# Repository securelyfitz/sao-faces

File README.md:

# sao-faces
'Faces' to be used along with ['arms'](https://github.com/securelyfitz/sao-arms) for a build-your-own badge. See the [microbadge](https://github.com/securelyfitz/microbadge) readme for more details about using them.

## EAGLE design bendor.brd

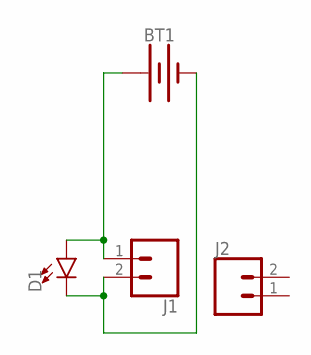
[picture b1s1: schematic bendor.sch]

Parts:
BT1: BATTERY-20MM_SMD_4LEGS; BATTCON_20MM_4LEGS
D1: LED3MM; LED_3MM
J1, J2: CONN_02LOCK; 1X02_LOCK
U$1: OREGON

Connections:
GND: BT1.NEGATIVE (-), D1.K (C), J1.2
VCC: BT1.POSITIVE@1 (+), BT1.POSITIVE@2 (+), BT1.POSITIVE@3 (+), BT1.POSITIVE@4 (+), D1.A, J1.1

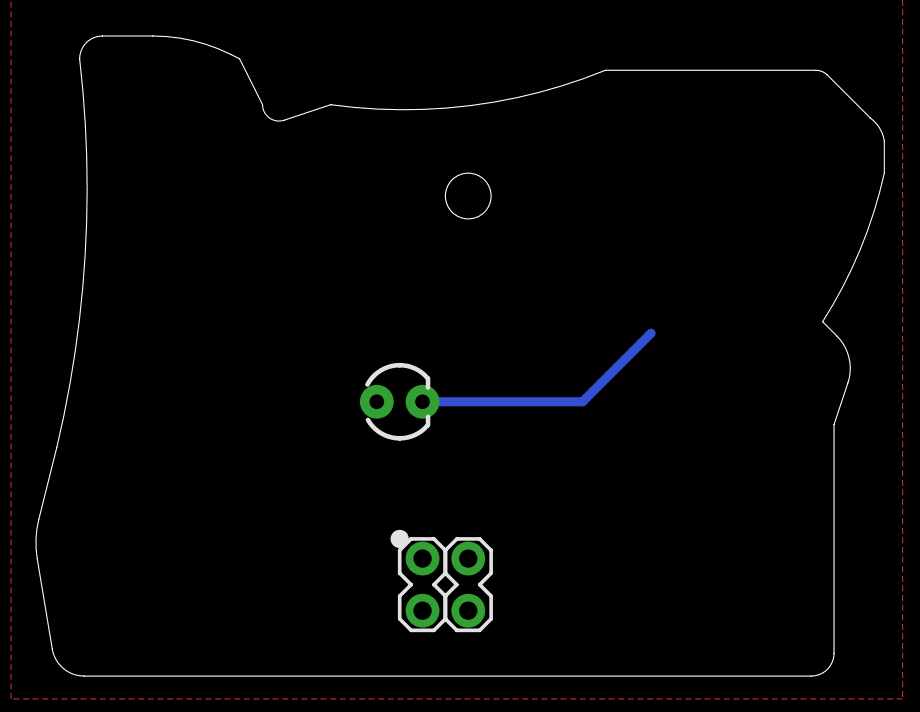
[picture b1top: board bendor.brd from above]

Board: 2 copper layers, 47.1 x 35.6 mm, 5 parts (1 on the bottom side), 2 nets.

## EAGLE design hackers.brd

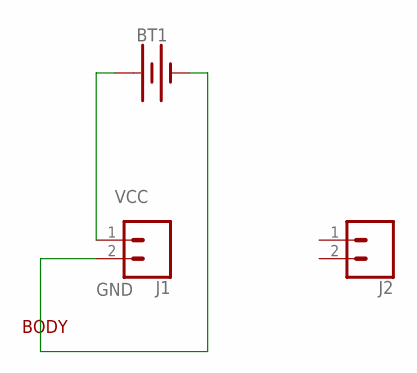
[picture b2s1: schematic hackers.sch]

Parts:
BT1: BATTERY-20MM_SMD; BATTCON_20MM
J1, J2: CONN_02LOCK; 1X02_LOCK
U$1: BODY; HACKERS

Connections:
GND: BT1.2 (-), J1.2
VCC: BT1.1 (+), J1.1

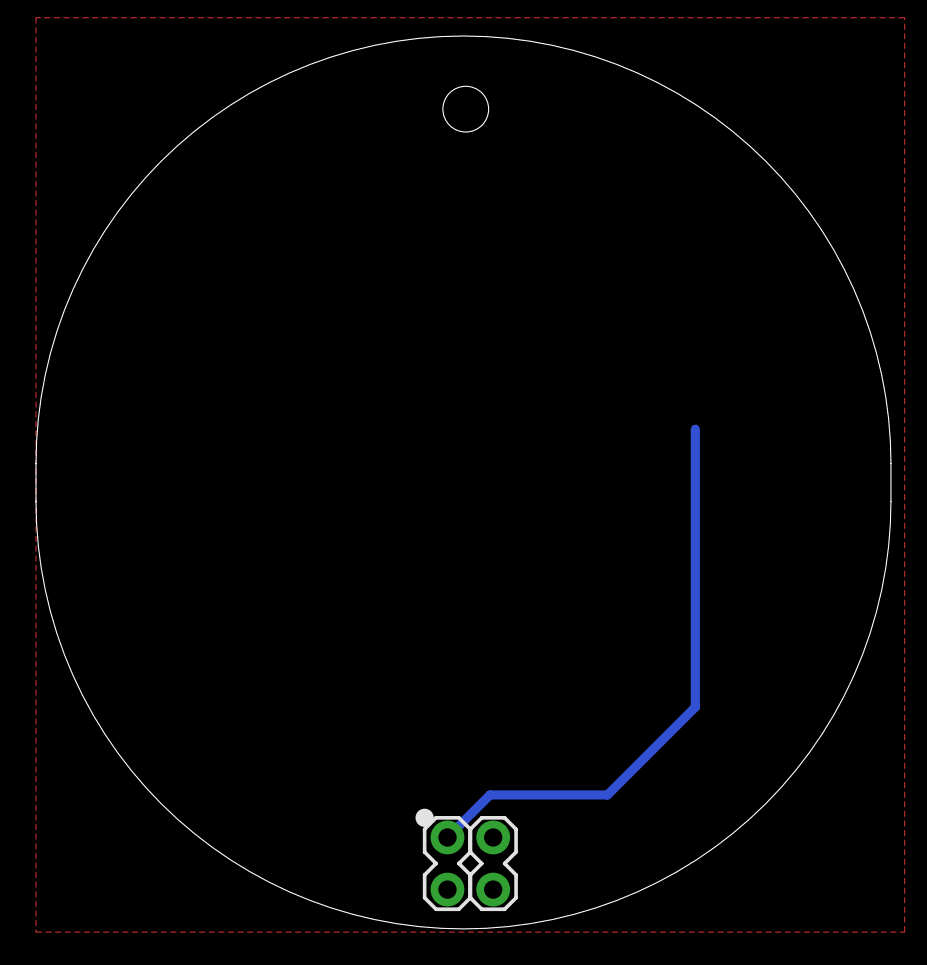
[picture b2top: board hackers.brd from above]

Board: 2 copper layers, 47.5 x 49.6 mm, 4 parts (1 on the bottom side), 2 nets.

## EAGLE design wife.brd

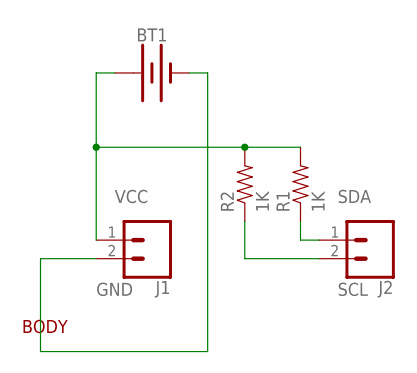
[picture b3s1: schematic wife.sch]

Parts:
BT1: BATTERY-20MM_SMD; BATTCON_20MM
J1, J2: CONN_02LOCK; 1X02_LOCK
R1, R2: 1K; AXIAL-0.3EZ
U$1: BODYWIFE; WIFE

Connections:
GND: BT1.2 (-), J1.2
SCL: J2.2, R2.P$1 (1)
SDA: J2.1, R1.P$1 (1)
VCC: BT1.1 (+), J1.1, R1.P$2 (2), R2.P$2 (2)

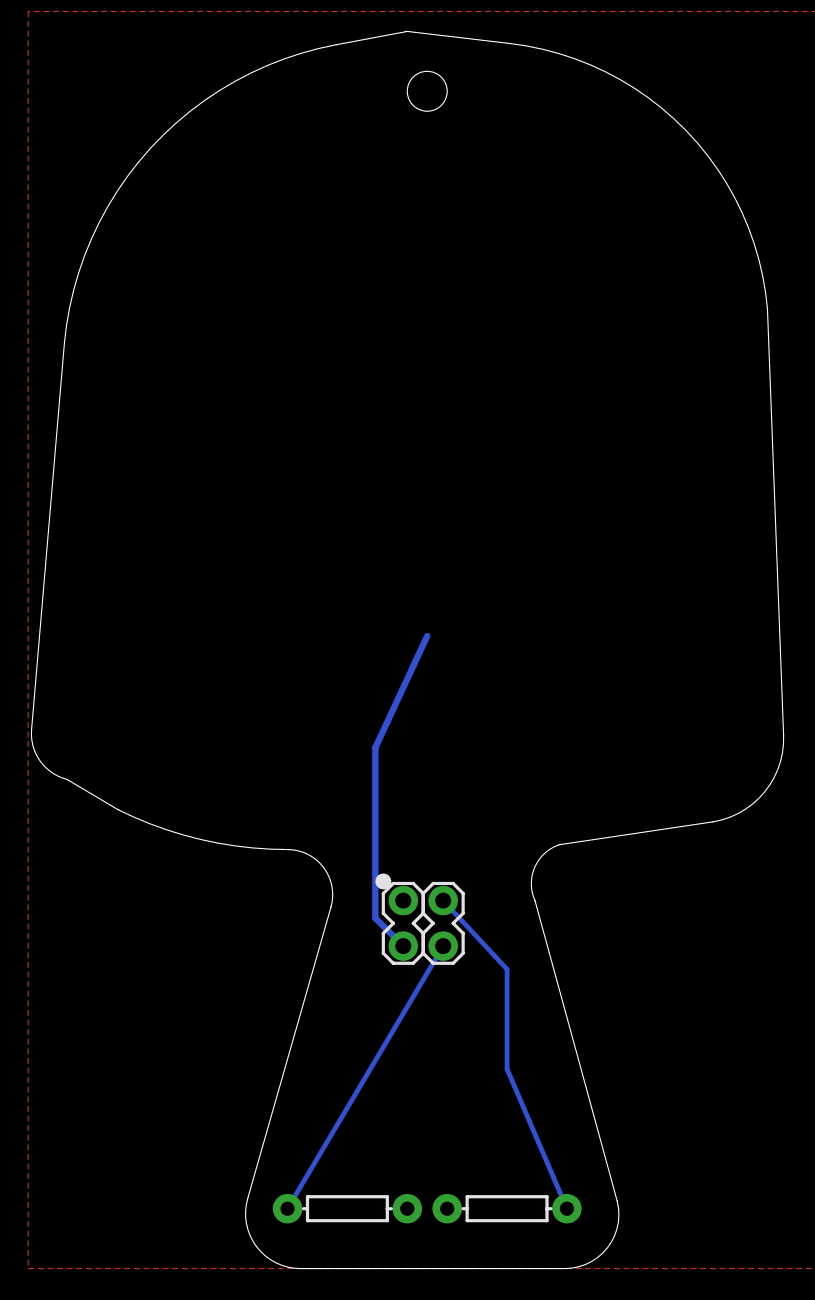
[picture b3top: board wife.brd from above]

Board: 2 copper layers, 47.9 x 78.7 mm, 6 parts (1 on the bottom side), 4 nets.

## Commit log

2018-08-09 initial copies of schematics, boards, cams, gerbers, and zips

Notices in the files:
parts and their libraries:
SparkFun-Connectors: Licensing: Creative Commons ShareAlike 4.0 International - https://creativecommons.org/licenses/by-sa/4.0
